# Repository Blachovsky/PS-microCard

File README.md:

<br>
<br>

# PS-microCard

**An RP2350-based PlayStation 1 memory card emulator with microSD-backed virtual cards, an OLED user interface and a custom PCB designed in KiCad.**

PS-microCard is an embedded hardware and firmware project that replaces a standard PlayStation 1 memory card with a programmable device capable of storing and switching multiple card images on a microSD card.

The project combines real-time console communication, RP2350 PIO, dual-core firmware, persistent storage, a small on-device UI, automated host-side testing, and custom electronics design.

> **Project status:** the current firmware builds for and is configured for a Raspberry Pi Pico 2 W development setup. The custom RP2350 PCB has been designed but not assembled or electrically validated, and its GPIO map, card-detect polarity, and OLED controller are not compatible with the current binary.

<p align="center"> 
<i> Custom PCB designed in KiCad. Hardware prototype not yet assembled.</i> 
</p>

[Watch the breadboard prototype demo](https://github.com/user-attachments/assets/f54d0bfc-f955-47ab-805d-b30cb20fdbb1)

## What it does

- Emulates a PlayStation 1 memory card at the console interface.
- Stores raw 131072-byte (`128 KiB`) `.MCR` memory-card images on a microSD card.
- Allows multiple virtual card images to be created, selected, and deleted.
- Provides an OLED menu controlled with two physical buttons.
- Displays directory-slot metadata from the selected image: filename, slot number, and derived block count.
- Keeps time-critical PlayStation communication separate from slower storage and UI work.
- Handles storage failures and SD-card removal without treating unconfirmed writes as safely persisted.

## Project highlights

### Real-time embedded firmware

The PlayStation memory-card interface is serviced on one RP2350 core, with PIO used for the low-level serial transport. Time-sensitive code is separated from filesystem and UI operations to reduce their interference with console communication; worst-case behavior still requires measurement on hardware.

### Dual-core architecture

The firmware splits responsibilities between the two RP2350 cores:

- **Core 0** — PlayStation bus handling and memory-card emulation.
- **Core 1** — microSD persistence, image management, OLED UI, and button input.

This separation keeps latency-sensitive work predictable while allowing the device to perform filesystem operations in parallel.

### Failure-aware persistence

Game saves are first reflected in the in-memory card image and are then persisted to microSD by a background worker. The worker confirms modified frames only after write, sync, and close succeed. Its retry bookkeeping works while RAM is preserved, but the current top-level SD recovery path reloads `CARD000.MCR`; RAM-only writes are therefore not guaranteed to survive a detected storage failure or removal.

### Custom hardware

The repository includes a custom RP2350-based PCB designed in **KiCad**, together with the schematic, PCB layout, component footprints, symbols, and 3D models used by the design. It is currently a design artifact, not a supported firmware target.

### Automated testing and CI

The firmware currently includes **75 host-side tests**:

- **61 unit tests**
- **14 integration tests**

The integration suite exercises host-simulated flows across the PS1 protocol layer, in-memory card state, and persistence worker. It does not execute the production PIO programs, menu loop, real FatFs/SD stack, or physical dual-core hardware.

GitHub Actions automatically builds the RP2350 firmware and runs the complete host-side test suite on pushes and pull requests.

## Architecture at a glance

```mermaid
flowchart LR
    PS1[PlayStation 1]
    SD[(microSD<br/>raw MCR images)]
    OLED[OLED]
    BUTTONS[Buttons]

    subgraph MCU[RP2350 / current Pico 2 W target]
        subgraph C0[Core 0: time-critical path]
            PIO[PIO0 RX and TX]
            BUS[PS1 protocol engine]
        end
        RAM[(128 KiB card image<br/>and frame versions)]
        subgraph C1[Core 1: cooperative loop]
            WORKER[Persistence worker]
            IMAGES[Image manager]
            MENU[Menu and input]
        end
    end

    PS1 <--> PIO <--> BUS <--> RAM
    RAM --> WORKER --> SD
    SD --> IMAGES --> RAM
    BUTTONS --> MENU --> IMAGES
    MENU --> OLED
```

Detailed protocol behavior, timing considerations, concurrency design, persistence limits, and hardware status are documented in [`docs/`](docs/README.md).

## Repository structure

```text
PS-microCard/
├── firmware/              Embedded C firmware for the RP2350
│   ├── board/             Board and peripheral configuration
│   ├── drivers/           OLED and low-level device drivers
│   ├── menu/              OLED UI and menu controller
│   ├── micro_sd/          Image management and persistence worker
│   ├── ps1/               PS1 memory-card protocol and PIO transport
│   └── tests/             Host-side unit and integration tests
├── hardware/              KiCad schematic, PCB and project libraries
├── docs/                  Technical project documentation
└── .github/workflows/     Firmware build and test automation
```

## Technology stack

| Area | Technologies |
| --- | --- |
| MCU | RP2350 / Raspberry Pi Pico 2 W development target |
| Firmware | C11, Raspberry Pi Pico SDK |
| Real-time I/O | RP2350 PIO, GPIO |
| Concurrency | RP2350 multicore |
| Storage | microSD, FatFs |
| User interface | Current setup: DFRobot DFR0650 / SSD1306 128×64 OLED and two buttons; custom PCB: DEP128064C2-W / SH1106G, not yet ported |
| Hardware design | KiCad |
| Testing | Ceedling, Unity, CMock |
| CI | GitHub Actions |
| Build system | CMake, Ninja |

## Testing

Host-side tests are intentionally used to verify as much firmware behavior as possible without requiring physical hardware. Hardware-specific boundaries such as GPIO, timing, and the filesystem are replaced with test doubles where appropriate, while production modules are compiled together for integration scenarios.

Examples of covered scenarios include:

- normal PlayStation write/read flows,
- persistence across a simulated firmware restart,
- multiple writes before storage synchronization,
- filesystem write and sync failures,
- SD-card removal during a write,
- worker-level replay after a simulated reconnect while the harness preserves RAM,
- switching between virtual card images without exposing a partial image.

These tests do not establish production PIO timing, physical SD behavior, real multicore scheduling, or the menu-driven recovery path. See the test documentation for the exact boundary.

See [`firmware/tests/README.md`](firmware/tests/README.md) for the complete test matrix and instructions for running individual test groups.

## Building the firmware

### Recommended setup: Visual Studio Code

The easiest development setup uses the official **Raspberry Pi Pico** extension for Visual Studio Code. It can install and configure the Pico SDK, ARM toolchain, CMake, Ninja, and device-programming tools.

The current project configuration uses:

- Pico SDK **2.2.0**
- ARM toolchain **14_2_Rel1**
- Raspberry Pi Pico 2 W (`pico2_w`) as the development target

> The custom PCB is not supported by this build configuration. Porting it requires a board definition and changes to the PS1 PIO pin mapping, SD/card-detect pins and polarity, buttons, and OLED driver/reset handling.

### Linux prerequisites

On Ubuntu, install the required tools and libraries with:

```bash
sudo apt update
sudo apt install git python3 tar gdb-multiarch libftdi1-2 libhidapi-hidraw0
```

To use **Run Project**, **Flash**, and debugging without `sudo`, install the appropriate `udev` rules for picotool and OpenOCD. See the [Raspberry Pi Pico VS Code extension documentation](https://github.com/raspberrypi/pico-vscode#requirements-by-os) for details.

### 1. Clone the repository with submodules

```console
git clone --recurse-submodules https://github.com/Blachovsky/PS-microCard.git
cd PS-microCard
```

If the repository was cloned without submodules:

```console
git submodule update --init --recursive
```

### 2. Open the firmware directory

Open `firmware/` rather than the repository root in VS Code:

```console
code firmware
```

Install the recommended **Raspberry Pi Pico** extension (`raspberry-pi.raspberry-pi-pico`) if VS Code does not offer to install it automatically.

### 3. Import the project if necessary

The extension should normally detect the project automatically. If it does not:

1. Open the **Raspberry Pi Pico** panel.
2. Select **Import Project**.
3. Choose the `firmware` directory.
4. Select Pico SDK `2.2.0`, toolchain `14_2_Rel1`, and **Pico 2 W** (`pico2_w`).
5. Leave CMake Tools integration disabled.
6. Complete the import and allow the extension to configure the project.

### 4. Build and run

- **Compile Project** builds the firmware and generates `firmware/build/main.uf2`.
- **Run Project** flashes and starts the firmware on a connected board.
- **Debug Project** starts an SWD debugging session using a compatible probe.

For the first USB flash, the board may need to be connected while holding **BOOTSEL**.

## Running host-side tests

The test suite is located in [`firmware/tests`](firmware/tests).

On Linux or macOS:

```bash
cd firmware/tests
bundle config set --local path vendor/bundle
bundle install
./run_tests.sh test:all
```

On Windows:

```powershell
cd firmware/tests
bundle config set --local path vendor/bundle
bundle install
.\run_tests.cmd test:all
```

## Documentation

The [`docs/`](docs/README.md) index links the current engineering documentation for architecture, PS1 protocol behavior, concurrency, UI behavior, hardware status.

## License

The PS-microCard project uses separate licenses for software and hardware.

* **Firmware and software:** see [`LICENSE`](license/LICENSE.md).
* **Hardware design:** licensed under the CERN Open Hardware Licence Version 2 – strongly reciprocal (`CERN-OHL-S-2.0`). See [`LICENSE-HARDWARE`](license/LICENSE-HARDWARE.md).

Third-party components remain subject to their respective licenses. See
[`THIRD_PARTY_NOTICES.md`](license/THIRD_PARTY_NOTICES.md) for details.

---

This project is primarily an exploration of **embedded systems engineering, real-time communication, storage, firmware testing, and custom hardware design** on the RP2350 platform.

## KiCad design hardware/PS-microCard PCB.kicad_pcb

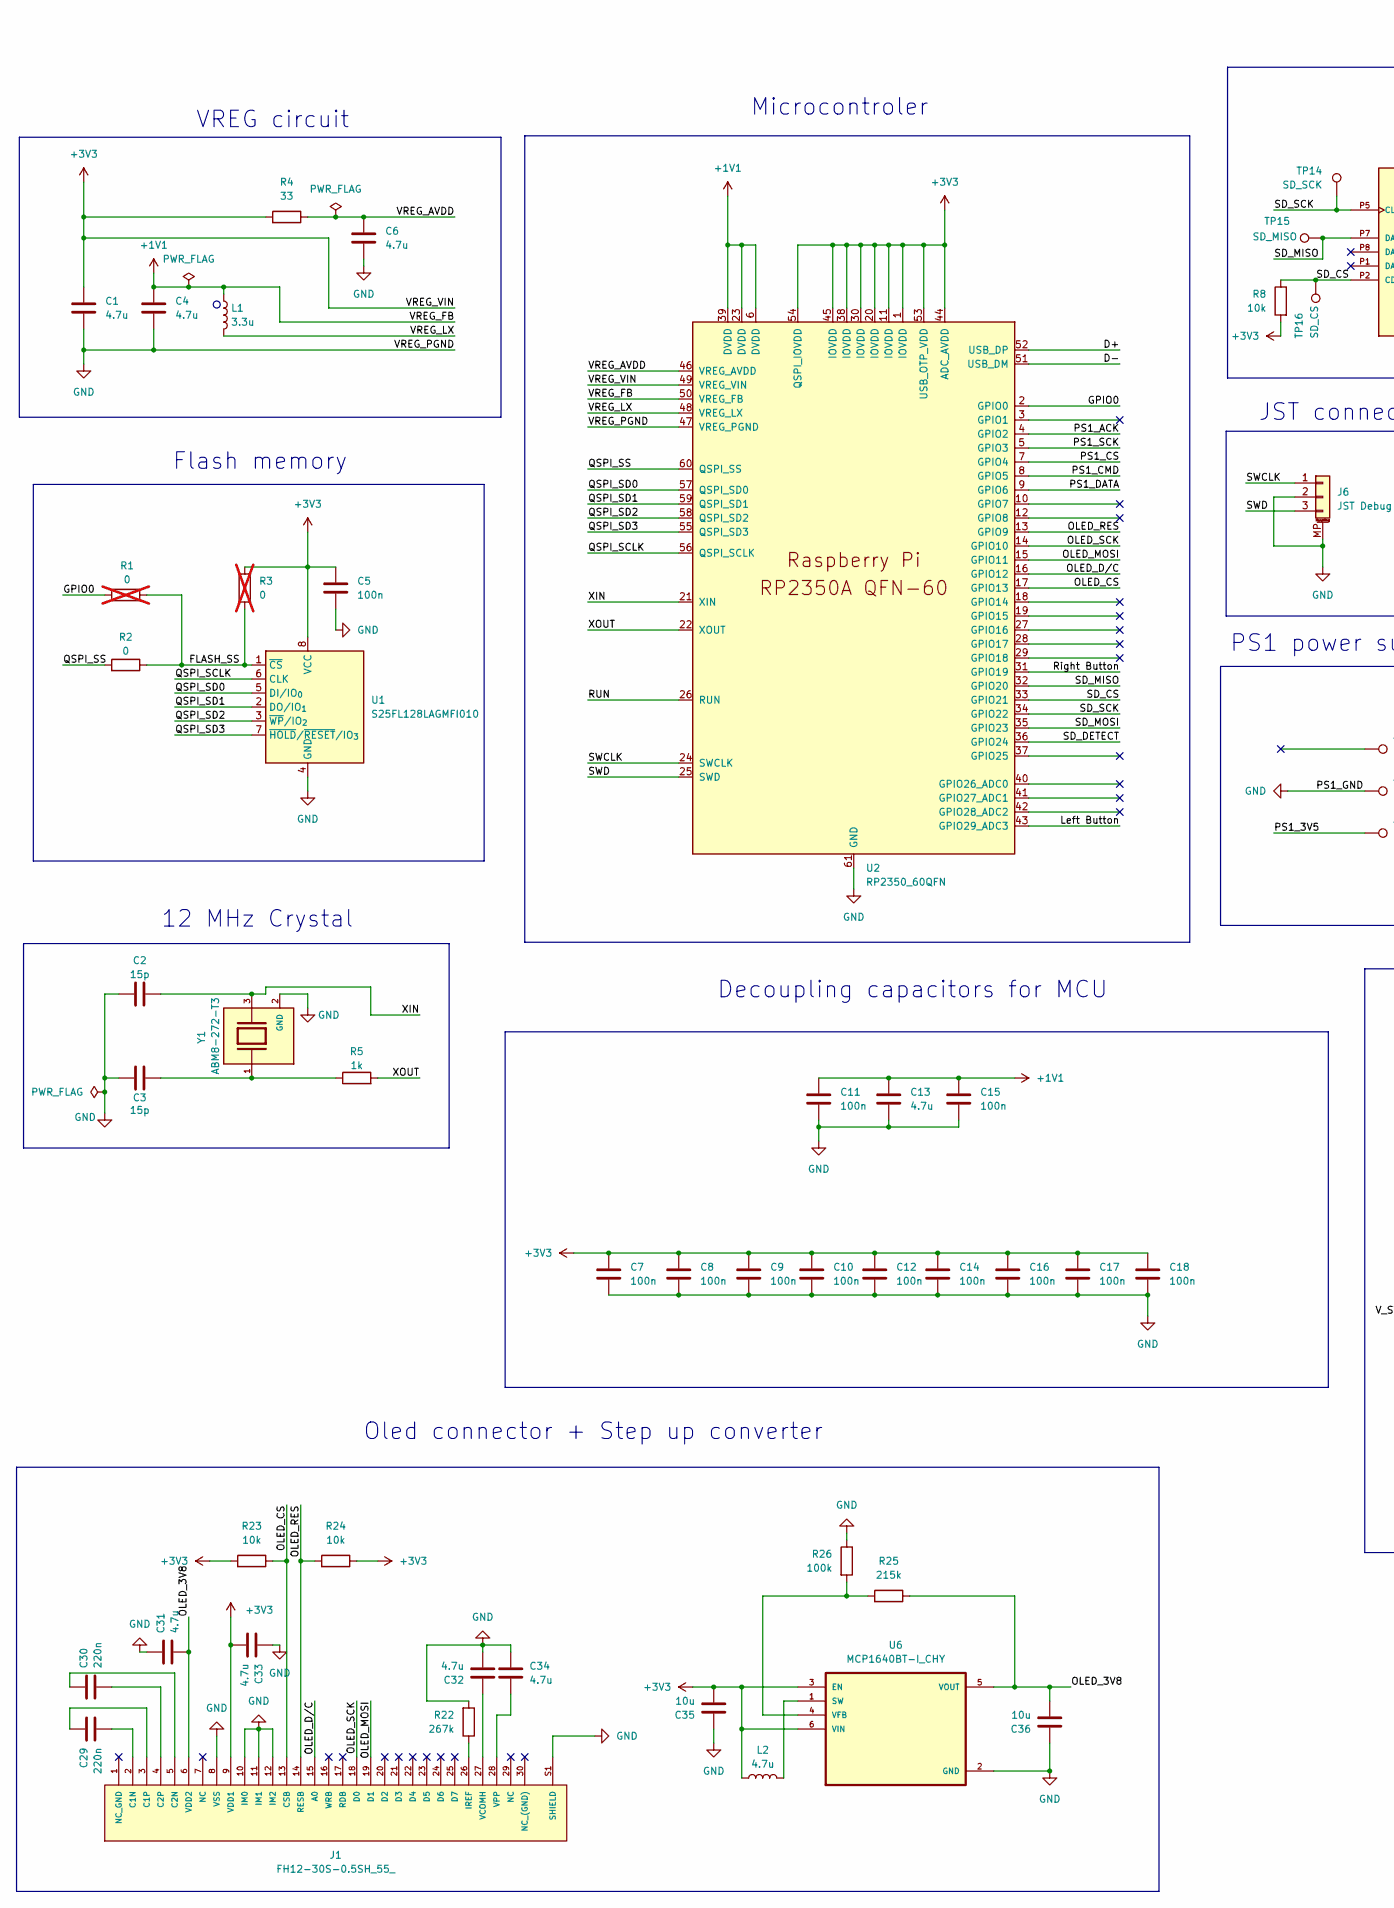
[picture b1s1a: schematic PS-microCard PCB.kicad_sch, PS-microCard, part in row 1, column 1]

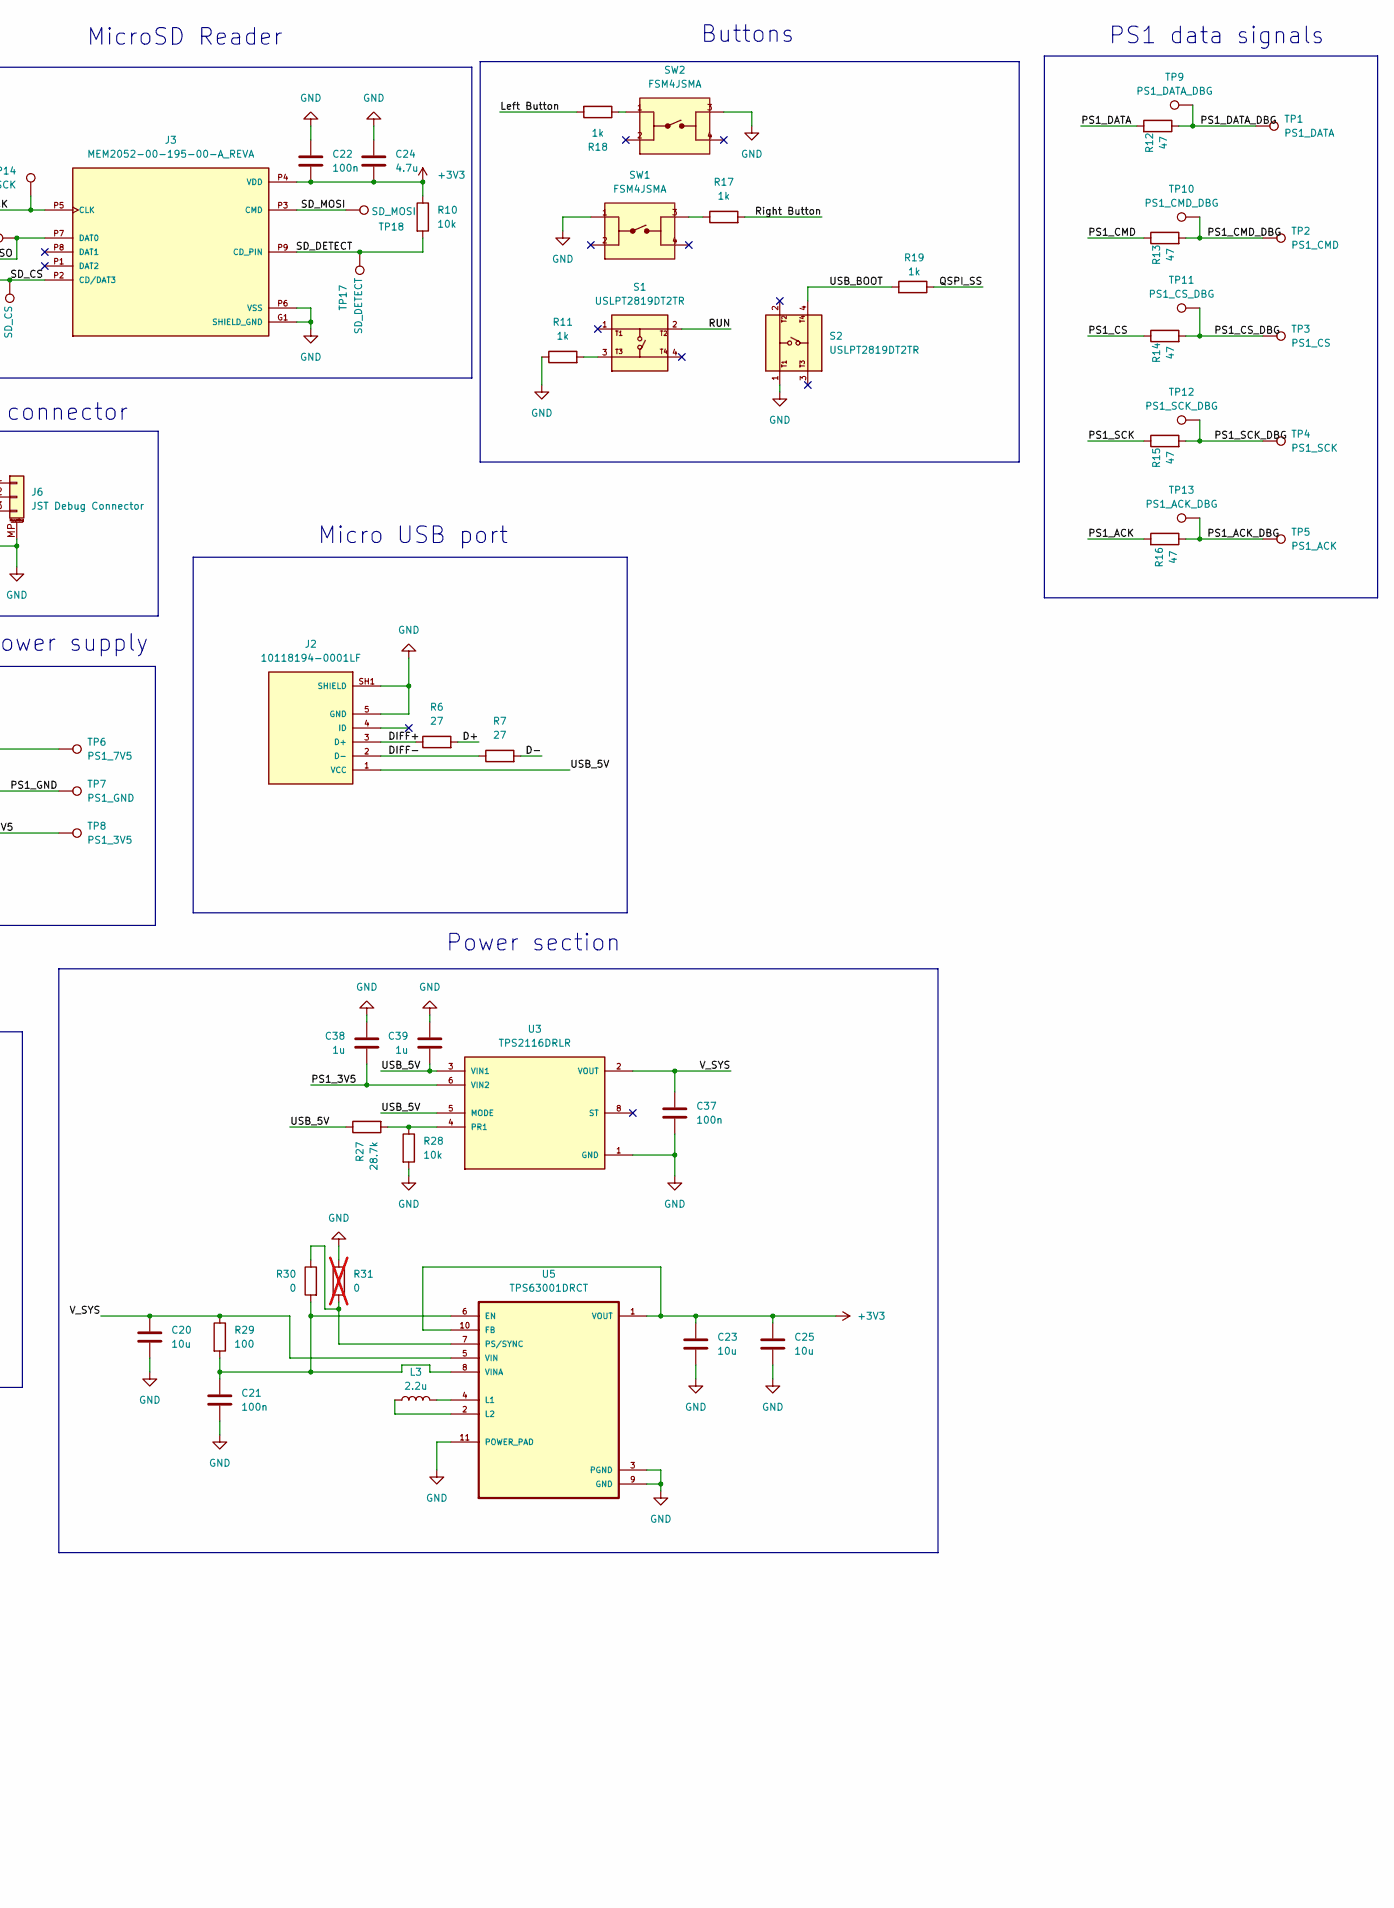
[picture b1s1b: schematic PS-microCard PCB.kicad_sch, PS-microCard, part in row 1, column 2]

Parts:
C1, C4: 4.7u; C_0402_1005Metric_small_pads
C2, C3: 15p; C_0402_1005Metric_Pad0.74x0.62mm_HandSolder
C5, C7, C8, C9, C10, C11, C12, C14, C15, C16, C17, C18, C21, C22, C37: 100n; C_0402_1005Metric_Pad0.74x0.62mm_HandSolder
C6, C13, C24, C31, C32, C33, C34: 4.7u; C_0402_1005Metric_Pad0.74x0.62mm_HandSolder
C20, C23, C25, C35, C36: 10u; C_0805_2012Metric_Pad1.18x1.45mm_HandSolder
C29, C30: 220n; C_0402_1005Metric_Pad0.74x0.62mm_HandSolder
C38, C39: 1u; C_0402_1005Metric_Pad0.74x0.62mm_HandSolder
J1: FH12-30S-0.5SH_55_; HIROSE_FH12-30S-0.5SH_55_
J2: 10118194-0001LF; AMPHENOL_10118194-0001LF; PARTREV D
J3: MEM2052-00-195-00-A_REVA; GCT_MEM2052-00-195-00-A_REVA; PARTREV A
J6: JST Debug Connector; JST_SH_SM03B-SRSS-TB_1x03-1MP_P1.00mm_Horizontal
L1: 3.3u; L_pol_2016
L2: 4.7u; L_APV_ANR4018
L3: 2.2u; IND_LQH3NPN2R2MMEL
R1, R3: 0; R_0402_1005Metric; not fitted
R2, R30: 0; R_0402_1005Metric_Pad0.72x0.64mm_HandSolder
R4: 33; R_0402_1005Metric_Pad0.72x0.64mm_HandSolder
R5, R11, R17, R18, R19: 1k; R_0402_1005Metric_Pad0.72x0.64mm_HandSolder
R6, R7: 27; R_0402_1005Metric_Pad0.72x0.64mm_HandSolder
R8, R10, R23, R24, R28: 10k; R_0402_1005Metric_Pad0.72x0.64mm_HandSolder
R12, R13, R14, R15, R16: 47; R_0402_1005Metric_Pad0.72x0.64mm_HandSolder
R22: 267k; R_0402_1005Metric_Pad0.72x0.64mm_HandSolder
R25: 215k; R_0402_1005Metric_Pad0.72x0.64mm_HandSolder
R26: 100k; R_0402_1005Metric_Pad0.72x0.64mm_HandSolder
R27: 28.7k; R_0402_1005Metric_Pad0.72x0.64mm_HandSolder
R29: 100; R_0402_1005Metric_Pad0.72x0.64mm_HandSolder
R31: 0; R_0402_1005Metric_Pad0.72x0.64mm_HandSolder; not fitted
S1, S2: USLPT2819DT2TR; SW_USLPT2819DT2TR; PARTREV P
SW1, SW2: FSM4JSMA; TE_FSM4JSMA; PARTREV V
TP1: PS1_DATA; Pad_kontaktowy_PS1_dane
TP2: PS1_CMD; Pad_kontaktowy_PS1_dane
TP3: PS1_CS; Pad_kontaktowy_PS1_dane
TP4: PS1_SCK; Pad_kontaktowy_PS1_dane
TP5: PS1_ACK; Pad_kontaktowy_PS1_dane
TP6: PS1_7V5; Pad_kontaktowy_PS1_zasilanie
TP7: PS1_GND; Pad_kontaktowy_PS1_zasilanie
TP8: PS1_3V5; Pad_kontaktowy_PS1_zasilanie
TP9: PS1_DATA_DBG; TestPoint_Pad_D1.0mm
TP10: PS1_CMD_DBG; TestPoint_Pad_D1.0mm
TP11: PS1_CS_DBG; TestPoint_Pad_D1.0mm
TP12: PS1_SCK_DBG; TestPoint_Pad_D1.0mm
TP13: PS1_ACK_DBG; TestPoint_Pad_D1.0mm
TP14: SD_SCK; TestPoint_Pad_D1.0mm
TP15: SD_MISO; TestPoint_Pad_D1.0mm
TP16: SD_CS; TestPoint_Pad_D1.0mm
TP17: SD_DETECT; TestPoint_Pad_D1.0mm
TP18: SD_MOSI; TestPoint_Pad_D1.0mm
U1: S25FL128LAGMFI010; SOIC-8_5.3x5.3mm_P1.27mm
U2: RP2350_60QFN; RP2350-QFN-60-1EP_7x7_P0.4mm_EP3.4x3.4mm_ThermalVias
U3: TPS2116DRLR; PARTREV A
U5: TPS63001DRCT
U6: MCP1640BT-I_CHY; SOT95P280X145-6N; DigiKey_Part_Number MCP1640BT-I/CHYCT-ND
Y1: ABM8-272-T3; XTAL_ABM8-272-T3; PARTREV 07-29-20

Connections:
+1V1: C4.1, C11.1, C13.1, C15.1, L1.1, U2.6 (DVDD), U2.23 (DVDD), U2.39 (DVDD), U2.50 (VREG_FB)
+3V3: C1.1, C5.1, C7.1, C8.1, C9.1, C10.1, C12.1, C14.1, C16.1, C17.1, C18.1, C22.1, C23.1, C24.1, C25.1, C33.2, C35.2, J1.9 (VDD1), J3.P4 (VDD), L2.1, R3.1, R4.2, R8.2, R10.1, R23.2, R24.1, U1.8 (VCC), U2.1 (IOVDD), U2.11 (IOVDD), U2.20 (IOVDD), U2.30 (IOVDD), U2.38 (IOVDD), U2.44 (ADC_AVDD), U2.45 (IOVDD), U2.49 (VREG_VIN), U2.53 (USB_OTP_VDD), U2.54 (QSPI_IOVDD), U5.1 (VOUT), U5.10 (FB), U6.3 (EN), U6.6 (VIN)
/D+: R6.2, U2.52 (USB_DP)
/D-: R7.2, U2.51 (USB_DM)
/DIFF+: J2.3 (D+), R6.1
/DIFF-: J2.2 (D-), R7.1
/FLASH_SS: R1.1, R2.1, R3.2, U1.1 (~CS)
/GPIO0: R1.2, U2.2 (GPIO0)
/Left Button: R18.2, U2.43 (GPIO29_ADC3)
/OLED_3V8: C31.2, C36.2, J1.6 (VDD2), R25.1, U6.5 (VOUT)
/OLED_CS: J1.13 (CSB), R23.1, U2.17 (GPIO13)
/OLED_D/C: J1.15 (A0), U2.16 (GPIO12)
/OLED_MOSI: J1.19 (D1), U2.15 (GPIO11)
/OLED_RES: J1.14 (RESB), R24.2, U2.13 (GPIO9)
/OLED_SCK: J1.18 (D0), U2.14 (GPIO10)
/PS1_3V5: C38.2, TP8.1 (1_1), U3.6 (VIN2)
/PS1_ACK: R16.2, U2.4 (GPIO2)
/PS1_ACK_DBG: R16.1, TP5.1 (1_1), TP13.1 (1_1)
/PS1_CMD: R13.1, U2.8 (GPIO5)
/PS1_CMD_DBG: R13.2, TP2.1 (1_1), TP10.1 (1_1)
/PS1_CS: R14.1, U2.7 (GPIO4)
/PS1_CS_DBG: R14.2, TP3.1 (1_1), TP11.1 (1_1)
/PS1_DATA: R12.2, U2.9 (GPIO6)
/PS1_DATA_DBG: R12.1, TP1.1 (1_1), TP9.1 (1_1)
/PS1_SCK: R15.1, U2.5 (GPIO3)
/PS1_SCK_DBG: R15.2, TP4.1 (1_1), TP12.1 (1_1)
/QSPI_SCLK: U1.6 (CLK), U2.56 (QSPI_SCLK)
/QSPI_SD0: U1.5 (DI/IO_{0}), U2.57 (QSPI_SD0)
/QSPI_SD1: U1.2 (DO/IO_{1}), U2.59 (QSPI_SD1)
/QSPI_SD2: U1.3 (~WP/IO_{2}), U2.58 (QSPI_SD2)
/QSPI_SD3: U1.7 (~HOLD/~RESET/IO_{3}), U2.55 (QSPI_SD3)
/QSPI_SS: R2.2, R19.1, U2.60 (QSPI_SS)
/RUN: S1.2, U2.26 (RUN)
/Right Button: R17.2, U2.31 (GPIO19)
/SD_CS: J3.P2 (CD/DAT3), R8.1, TP16.1 (1_1), U2.33 (GPIO21)
/SD_DETECT: J3.P9 (CD_PIN), R10.2, TP17.1 (1_1), U2.36 (GPIO24)
/SD_MISO: J3.P7 (DAT0), TP15.1 (1_1), U2.32 (GPIO20)
/SD_MOSI: J3.P3 (CMD), TP18.1 (1_1), U2.35 (GPIO23)
/SD_SCK: J3.P5 (CLK), TP14.1 (1_1), U2.34 (GPIO22)
/SWCLK: J6.1, U2.24 (SWCLK)
/SWD: J6.3, U2.25 (SWD)
/USB_5V: C39.2, J2.1 (VCC), R27.1, U3.3 (VIN1), U3.5 (MODE)
/USB_BOOT: R19.2, S2.4
/VREG_AVDD: C6.1, R4.1, U2.46 (VREG_AVDD)
/VREG_LX: L1.2, U2.48 (VREG_LX)
/V_SYS: C20.1, C37.1, R29.1, U3.2 (VOUT), U3.7 (VOUT), U5.5 (VIN)
/XIN: C2.2, U2.21 (XIN), Y1.3
/XOUT: R5.2, U2.22 (XOUT)
GND: C1.2, C2.1, C3.1, C4.2, C5.2, C6.2, C7.2, C8.2, C9.2, C10.2, C11.2, C12.2, C13.2, C14.2, C15.2, C16.2, C17.2, C18.2, C20.2, C21.2, C22.2, C23.2, C24.2, C25.2, C31.1, C32.2, C33.1, C34.1, C35.1, C36.1, C37.2, C38.1, C39.1, J1.8 (VSS), J1.10 (IM0), J1.11 (IM1), J1.12 (IM2), J1.S1 (SHIELD), J1.S2 (SHIELD), J2.5 (GND), J2.SH1 (SHIELD), J2.SH2 (SHIELD), J2.SH3 (SHIELD), J2.SH4 (SHIELD), J2.SH5 (SHIELD), J2.SH6 (SHIELD), J3.G1 (SHIELD_GND), J3.G2 (SHIELD_GND), J3.G3 (SHIELD_GND), J3.G4 (SHIELD_GND), J3.P6 (VSS), J6.2, J6.MP (MountPin), R11.1, R22.2, R26.1, R28.2, R31.1, S2.1, SW1.1, SW2.3, TP7.1 (1_1), U1.4 (GND), U2.47 (VREG_PGND), U2.61 (GND), U3.1 (GND), U5.3 (PGND), U5.9 (GND), U5.11 (POWER_PAD), U6.2 (GND), Y1.2 (GND), Y1.4 (GND)
unnamed: C3.2, R5.1, Y1.1
unnamed: C29.2, J1.2 (C1N)
unnamed: C29.1, J1.3 (C1P)
unnamed: C30.1, J1.5 (C2N)
unnamed: C30.2, J1.4 (C2P)
unnamed: J1.26 (IREF), R22.1
unnamed: C32.1, J1.27 (VCOMH)
unnamed: C34.2, J1.28 (VPP)
unnamed: R11.2, S1.3
unnamed: R17.1, SW1.3
unnamed: R18.1, SW2.1
unnamed: R27.2, R28.1, U3.4 (PR1)
unnamed: C21.1, R29.2, R30.2, U5.6 (EN), U5.8 (VINA)
unnamed: L3.2, U5.4 (L1)
unnamed: L3.1, U5.2 (L2)
unnamed: R30.1, R31.2, U5.7 (PS/SYNC)
unnamed: L2.2, U6.1 (SW)
unnamed: R25.2, R26.2, U6.4 (VFB)

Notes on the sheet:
Power section
Buttons
12 MHz Crystal
Decoupling capacitors for MCU
MicroSD Reader
Oled connector + Step up converter
PS1 data signals
VREG circuit
JST connector
Microcontroler
PS1 power supply
Flash memory
Micro USB port

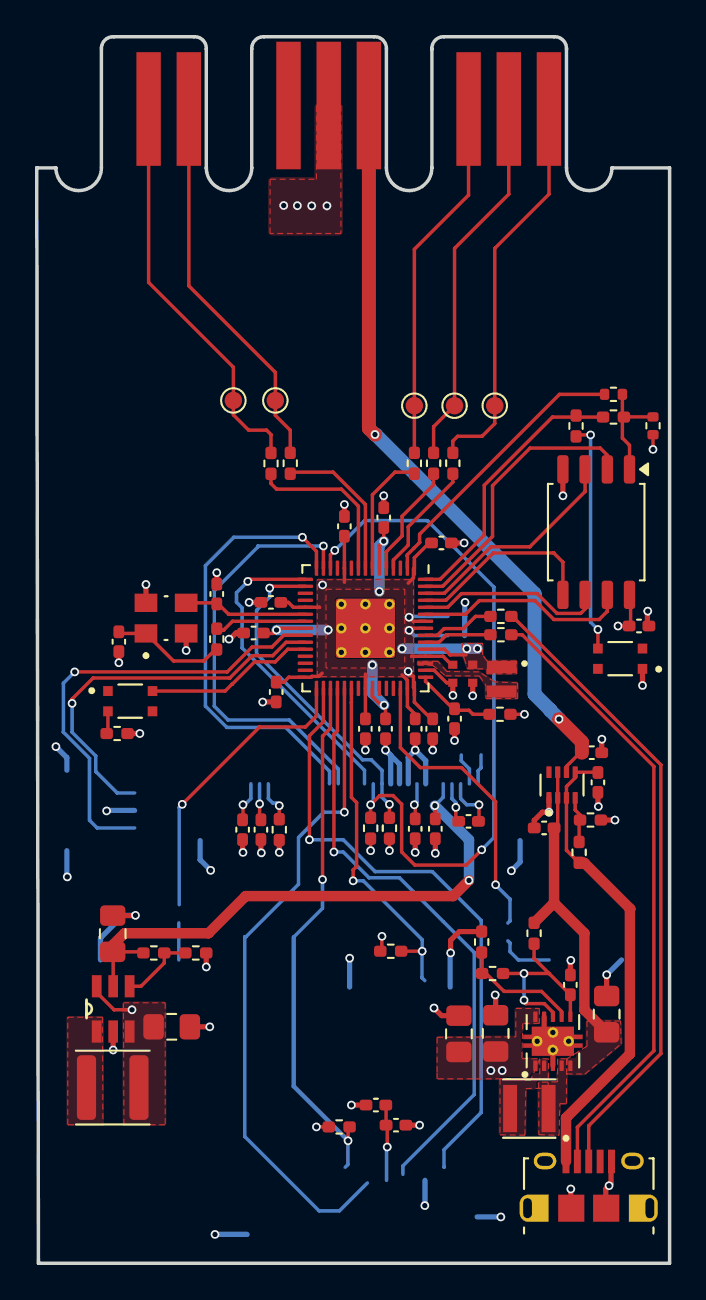
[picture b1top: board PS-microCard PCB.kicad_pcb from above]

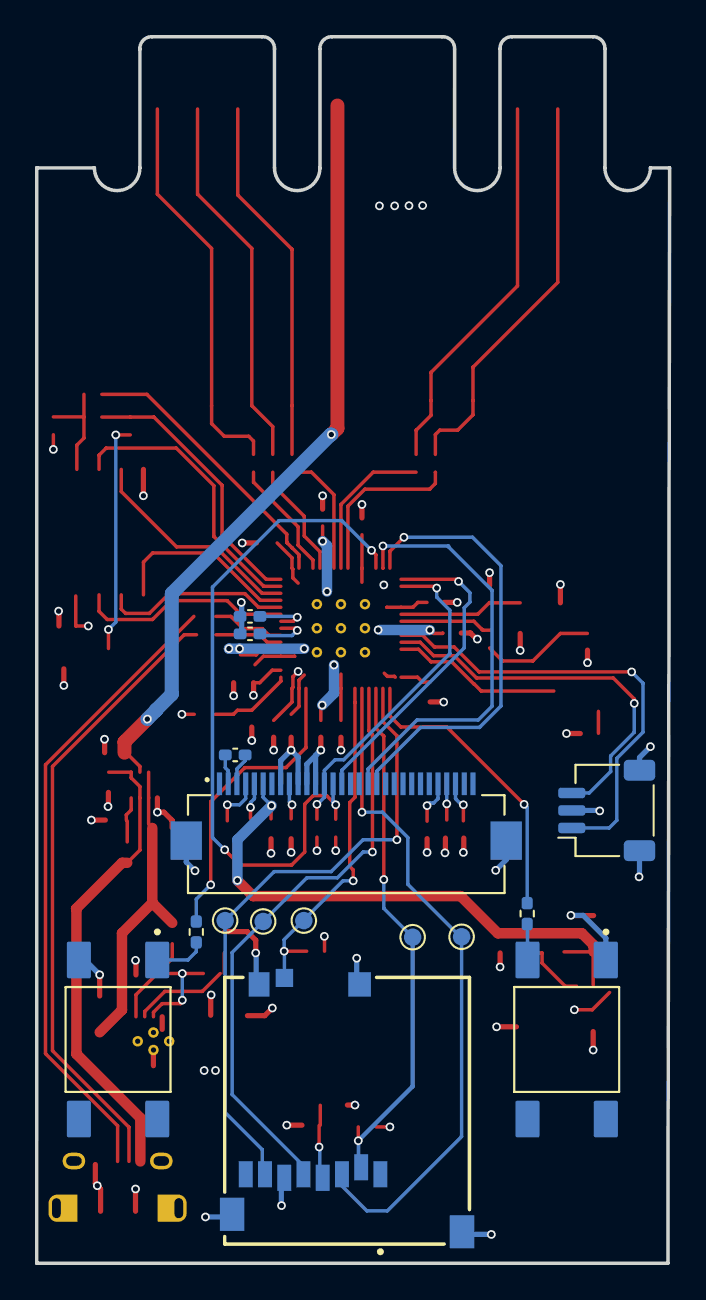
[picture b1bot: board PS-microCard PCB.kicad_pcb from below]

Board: 4 copper layers, 36.2 x 70.2 mm, 98 parts (15 on the bottom side), 67 nets.

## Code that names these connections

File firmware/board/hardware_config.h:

#ifndef HARDWARE_CONFIG_H
#define HARDWARE_CONFIG_H

/* Board pinout and peripheral configuration. */

#include <stddef.h>

#include "ps1/ps1_card_geometry.h"
#include "sd_card.h"

// =====================
// microSD SPI0 pins
// =====================
#define SD_SPI_PORT     spi0
#define SD_MISO_PIN     16
#define SD_MOSI_PIN     19
#define SD_SCK_PIN      18
#define SD_CS_PIN       17
#define SD_DETECT_PIN   20

// Pololu 2597 CD is pulled high when a card is present and grounded when empty.
#define SD_DETECT_PRESENT_LEVEL 1

#define SD_BAUD_RATE    (8 * 1000 * 1000)

// =====================
// DFR0650 OLED / SSD1306 on SPI1
// =====================
// DFR0650 labels: SCL = SCK, SDA = MOSI.
#define OLED_SPI_PORT   spi1
#define OLED_SCK_PIN    10
#define OLED_MOSI_PIN   11
#define OLED_DC_PIN     12
#define OLED_CS_PIN     13

#define OLED_BAUD_RATE  (4 * 1000 * 1000)
#define OLED_WIDTH      128
#define OLED_HEIGHT     64

// Set to 1 if the display is mounted upside down.
#define OLED_ROTATE_180 0

// =====================
// Two-button menu
// =====================
// Tact switches should connect the GPIO pin to GND. Internal pull-ups are used.
#define MENU_NEXT_PIN   8
#define MENU_SELECT_PIN 9

// =====================
// PS1 Memory Card pins
// =====================
#define PS1_DATA_PIN    2
#define PS1_CMD_PIN     3

#define PS1_CS_PIN      4
#define PS1_SCK_PIN     5
#define PS1_ACK_PIN     6

#define PS1_ACK_PULSE_US     3
#define PS1_SAMPLE_DELAY_US  2

// =====================
// Functions required by PS1 pins
// =====================
void ps1emu_gpio_init(void);

// =====================
// Functions required by the SD library
// =====================
size_t sd_get_num(void);
sd_card_t *sd_get_by_num(size_t num);

#endif // HARDWARE_CONFIG_H

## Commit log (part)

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2026-04-25 Stage 1: Writing to and reading from an SD card
2026-04-25 Adding external lib
2026-04-27 Revert "Adding external lib"
    This reverts commit 0dfdecdcd2e766a9eb29a94532c825f25dd4e673.
2026-04-27 submodule repo fix
2026-04-27 proper submodule addition
2026-05-01 Stage 2: Read single frame from PS memmory card
2026-05-02 Stage 3: Copy the entire contents of the PS1 card to the microSD card
2026-05-05 Stage 4 full data restore from microSD to PS1 card
2026-06-05 add gitignore for latex documentation
2026-06-24 Stage 5: First Memory Card Emulator
2026-06-24 latex template for documentation
